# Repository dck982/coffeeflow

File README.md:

# coffeeflow

Modification d'une **Profitec Go** pour du *flow profiling* et du *brew by weight* : l'infusion se lance depuis un écran tactile, le débit et la pression se pilotent par la vitesse d'une **pompe à engrenage**, et l'infusion s'arrête toute seule au poids cible.

## Machine d'origine

- Vanne solénoïde trois voies + pompe vibratoire OLAB Silent Green 35 W (**remplacée** par une pompe à engrenage, voir plus bas) + boiler
- Petit boîtier PID : consigne / mesure de température du boiler, chrono
- Vanne OPV pour limiter la pression
- Plomberie en **1/8"**
- Connexions électriques internes : cosses à languette **FASTON 6,3 × 0,8 mm** (pas de piggyback : la dérivation se fait dans un boîtier imprimé)
- Deux compartiments : **technique** (hydraulique, boiler, groupe, électricité) et **réservoir d'eau**
- Bouton **brew** en façade (Ø 16 mm) : démarrait vanne + pompe. **Supprimé** — le trou sert de passe-câble vers l'écran
- LED de façade : ses cosses FASTON ont été réutilisées, la LED est réalimentée depuis le boîtier de l'alimentation

## Ce que la modification ajoute

La modification pilote la pompe, la vanne et la résistance de chaudière :

1. **Pompe** — la pompe vibratoire est remplacée par une **pompe à engrenage SOVOFLO MPB003** (moteur BLDC 24 V, 40 W, 0,1 ml par tour), installée le 12 novembre 2026. Volumétrique et sans pulsation, son débit suit la vitesse, commandée par une consigne 0–5 V et relue sur son tachymètre. Détail : [pompe-engrenage.md](docs/pompe-engrenage.md).
2. **Vanne solénoïde** — un triac sur la carte `combined` ouvre et ferme le circuit d'infusion.
3. **Chaudière** — le SSR Keysolu/Maxwell fourni avec la machine commande la résistance de chauffe ; `combined` lui envoie sa commande 5 V.

Plus de bouton brew, plus de relais NC de « mode manuel » : la commande passe par l'écran. Le système est alimenté dès que l'**interrupteur principal** de la machine est enfoncé.

Deux retours capteurs, sur la carte `combined` :

- **Pression** sur la plomberie, en amont de la vanne (XDB401 analogique, 0,4–2,4 V)
- **Débit** en amont de la pompe, côté basse pression (le capteur ne tient que 3 bar)

La pompe donne en plus sa **vitesse** par son tachymètre, donc le volume déplacé, au glissement près.

La **température de la chaudière** vient de la sonde NTC vissée en G1/8 dans la chaudière. Son câble rejoint le boîtier de l'écran, proche de la sonde, où un ADS1115 la mesure via un pont alimenté par le **3V3 et le GND du port Sensor AD du Waveshare**. Voir [la calibration NTC/ADS1115](docs/ntc_ads1115_calibration.md).

Le **poids** vient d'une balance **Acaia Lunar** en **BLE**, lue par l'écran. La pesée du drip tray par cellule de charge est **abandonnée pour l'instant** (peser quelques grammes sur un plateau d'un kilo) — notes dans `docs/driptray.md` ; les pièces imprimées ont été retirées (commit 1aa13ed). Une nouvelle balance intégrée au drip tray est en conception (cellule 1 kg, carte `pcb/scale`, pièces `print/parts/scale_*`) : [tray-with-scale.md](docs/tray-with-scale.md).

## Architecture électronique

**Une alimentation 24 V, une carte maison, deux nœuds ESP32-S3.** Le 230 V ne sort pas de la machine.

```
             interrupteur principal (230 V L/N)
                          │
                  [boitier_ps_24v]   intérieur, face ouest, le long du réservoir
               Wago L/N · alim 24 V 96 W
                  │            │    └── L/N → LED de façade
               L/N (J2)     24 V (J7) ──────────────→ pompe à engrenage MPB003
                  │            │                      (embouts doubles dans J7)
             [boitier_ac + boitier_dc]
              carte combined : XIAO ESP32-S3 · buck 24 → 5 V · CAN
                  │
                  ├── J3  triac ────────→ vanne solénoïde (230 V)
                  ├── J8  5 V ──────────→ SSR chaudière ─→ résistance
                  ├── J9  2 optocoupleurs ⇄ consigne et tachymètre de la pompe
                  ├── J10 ADS1115 ←──── capteur de pression XDB401 (0,4–2,4 V)
                  ├── J6  GPIO ←──────── débitmètre Digmesa
                  └── J1  5 V + CAN ───→ [screen_*] Waveshare 4,3" ESP32-S3
                                          UI · Wi-Fi · BLE
                                          └── I2C ← ADS1115 ← NTC chaudière
```

| Nœud | Alias | Où | Rôle |
| --- | --- | --- | --- |
| **Waveshare 4,3" LCD Touch** (ESP32-S3-WROOM) | *screen*, *écran*, *waveshare* | façade, dans `screen_base` + `screen_wedge` | Interface utilisateur, algorithme d'infusion, **Wi-Fi et BLE** (Acaia Lunar) ; raccordement de la NTC chaudière via ADS1115 |
| **Seeed XIAO ESP32-S3** sur la carte **`combined`** | *xiao*, *combined*, *module capteurs*, *contrôleur* | intérieur, `boitier_ac` + `boitier_dc`, zone froide entre le module PID et le cadran manomètre | Capteurs (XDB401, Digmesa, tachymètre) et actionneurs (consigne de la pompe, vanne, commande du SSR chaudière) |

Les deux nœuds parlent **CAN**. L'écran est le seul à utiliser la radio.

Maquette Three.js de la machine (ouvrir dans le navigateur) : `docs/profitec_go.html`.

### Pourquoi un XIAO à l'intérieur

L'Atom Echo S3R de l'ancienne architecture est spécifié à **40 °C**. Le XIAO ESP32-S3 tient **85 °C**. Le compartiment technique monte à 45–50 °C : la marge de l'Atom est nulle, celle du XIAO est utilisable. L'écran Waveshare reste en façade, hors de cette enceinte.

---

## Boîtiers

| Boîtier | Pièces `print/parts/` | Où | Contenu |
| --- | --- | --- | --- |
| **PS 24 V** | `boitier_ps_24v`, `couvercle_ps_24v` | intérieur, contre la face **gauche** vue de face, le long de la séparation avec le réservoir | Alimentation 24 V, deux Wago 221-415 (L, N) ; le câble de l'écran le traverse |
| **AC + DC** | `boitier_ac`, `boitier_dc`, `couvercle_acdc` | intérieur, **zone froide** entre le module PID et le cadran manomètre | Carte `combined` : bande secteur dans `boitier_ac`, basse tension et aile 24 V dans `boitier_dc` |
| **UI** | `screen_base`, `screen_wedge` | façade de la machine | Écran Waveshare 4,3", ADS1115 et raccordement NTC ; emplacement AMS1117 inutilisé |

Les boîtiers **AC et DC sont côte à côte et reliés par leur couvercle**, qui est commun aux deux (`couvercle_acdc`, assemblage `ensemble_boitiers`). `boitier_pid` ne loge plus rien : c'est un pont qui tient le `cache_pid` contre l'ouverture de la machine.

La pompe est fixée par son équerre d'origine dans deux des trous de 6 mm de la plaque du fond de la machine, à 40 mm d'entraxe.

---

## Composants

| Rôle | Matériel retenu | Fiche |
| --- | --- | --- |
| UI / algo / radio | **Waveshare ESP32-S3-Touch-LCD-4.3** — 800 × 480, TJA1051T/3 CAN intégré, alim USB-C 5 V | `docs/datasheets/waveshare-4-3-lcd-touch.md` |
| Carte interne | **`combined`** (maison, JLCPCB) : **Seeed Studio XIAO ESP32-S3** enfiché, buck 24 → 5 V, TJA1051T/3, triac de vanne, interface optocouplée de la pompe, ADS1115 de pression | `pcb/combined/combined_design.md`, `docs/datasheets/xiao.pdf` |
| Pompe | **SOVOFLO MPB003BAAA** — engrenage, BLDC 24 V 40 W, 0,1 ml/tour, 12 bar au plus, raccords G1/8 | [pompe-engrenage.md](docs/pompe-engrenage.md) |
| Alimentation | Module ouvert **24 V, 4 A** (Aideepen, 96 W), fusible T2A interne | [pompe-engrenage.md](docs/pompe-engrenage.md#alimentation), [boitier-ps-24v.md](docs/boitier-ps-24v.md) |
| SSR chaudière | **Keysolu/Maxwell KS53 D-24Z20N-LQ**, fourni avec la machine ; en série entre la phase de l'interrupteur principal et la résistance, suivie de la protection thermique puis du neutre ; commande DC +/− depuis `combined` J8, FASTON mâles 4,8 mm | [Câblage](docs/cablage.md#ssr-de-chaudière-fourni-avec-la-machine) |
| Température chaudière | Sonde **NTC G1/8**, pont sur le port Sensor AD et breakout **ADS1115 16 bits** sur l'I2C de l'écran | [Calibration NTC/ADS1115](docs/ntc_ads1115_calibration.md) |
| Pression | **XDB401** analogique, 3,3 V, sortie 0,4–2,4 V, 0–12 bar, filetage **G1/8** | `docs/xdb401_swap.md` |
| Débit | **Digmesa FHKSC 932-9525-B**, buse **1,00 mm** | `docs/datasheets/flowmeter-digmesa.pdf`, `docs/debitmetres.md` |
| Poids | **Acaia Lunar**, BLE, lue par l'écran | — |
| Câble | **Helutherm 145** — 0,75 mm² en 230 V et en 24 V, 0,5 mm² pour le Digmesa, 0,25 mm² pour le 5 V et le CAN de l'écran ; puissance chaudière en 1 mm² | `docs/datasheets/helutherm145.pdf` |

Actionneur d'origine piloté : vanne solénoïde **OLAB 08252L50-A14-1A-G** (bobine 08000BH-J5IV, 15 VA, 220/230 V 50/60 Hz, orifice Ø 1,4 mm, joint FKM, laiton CW510L, NSF).

---

## La carte `combined`

Une seule carte réunit la partie 230 V (vanne) et la basse tension (XIAO, CAN, capteurs, commande de la pompe et du SSR chaudière). Elle reçoit le 24 V de l'alimentation et fait son propre 5 V, qu'elle renvoie à l'écran avec le CAN.

| Connecteur | Type | Vers |
| --- | --- | --- |
| **J1** | XH 4 | écran : GND, +5V, CAN_L, CAN_H |
| **J2** | HT3.96 2 | entrée 230 V, L et N |
| **J3** | HT3.96 2 | vanne solénoïde |
| **J6** | HT3.96 3 | Digmesa |
| **J7** | HT3.96 2 | entrée 24 V ; la pompe y est alimentée par des embouts doubles |
| **J8** | HT3.96 2 | commande du SSR chaudière |
| **J9** | XH 4 | signaux de la pompe : référence, consigne, tachymètre, 5 V de la pompe |
| **J10** | XH 3 | XDB401 |

J4 et J5, les prises I2C Grove de la carte `sensors`, n'existent plus. Brochage, schéma et choix des composants : `pcb/combined/combined_design.md`. Détail fil par fil : [cablage.md](docs/cablage.md).

**Pompe.** La consigne passe par un optocoupleur et un filtre RC (PWM à 1 kHz), le tachymètre revient par un second optocoupleur : les fils de signal de la pompe ne touchent jamais une masse ni une alimentation de la carte. Sans commande (démarrage, reset, XIAO absent), la consigne retombe à 0 et la pompe reste à l'arrêt.

**Bus CAN.** Paire torsadée de J1 jusqu'à l'écran, par le trou de l'ancien bouton brew. **Terminaisons 120 Ω aux deux bouts** : soudée sur `combined`, par jumper sur le Waveshare.

---

## Alimentation

L'**alimentation 24 V, 96 W** vit dans `boitier_ps_24v` et alimente **tout** : la pompe directement, et toute la basse tension par le buck de `combined`.

### 230 V

- **Phase et neutre** viennent de deux **cosses FASTON isolées** prises sur l'**interrupteur principal** de la machine : tant qu'il n'est pas enfoncé (clic mécanique), rien n'est sous tension.
- Les deux fils (**Helutherm 145 0,75 mm²**) vont dans les deux **Wago 221-415** de `boitier_ps_24v`, une pour L, une pour N.
- De ces Wago repartent trois paires 0,75 mm² : la **LED de façade**, l'**alimentation 24 V** (JST VH, position centrale vide) et **`combined` J2** (HT3.96).
- De **J3** repartent phase commutée et neutre vers la **vanne solénoïde** — **bleu / jaune**, FASTON 6,3 mm côté vanne.

### 24 V

- Deux fils **0,75 mm² rouge / noir** vont du bornier de l'alimentation à **`combined` J7**.
- Dans le boîtier HT3.96 de J7, chaque fil est serti avec le fil de même polarité de la pompe dans un **embout double 2 × 0,75 mm²** : la pompe est alimentée par J7, sans que son courant traverse les pistes de la carte.
- Le buck de `combined` fait le **5 V** du XIAO, du CAN, du Digmesa, de la commande du SSR chaudière et de l'**écran**, par J1 : paire 5 V / GND le long de la paire CAN, puis deux Wago 221-412 et un câble USB-C côté écran.
- Le pont NTC du boîtier de l'écran utilise le **3V3 / GND du port Sensor AD du Waveshare**.

---

## Capteurs

### Température chaudière — NTC G1/8

La sonde rejoint directement le boîtier de l'écran, voisin de la chaudière. Le **3V3 du port Sensor AD du Waveshare** rejoint la Wago NTC2, la NTC et l'entrée **A0** de l'ADS1115 ; le retour NTC rejoint la Wago NTC1, **A1** et une résistance de **4,7 kΩ** (4676 Ω étalonnés) vers le **GND du même port Sensor AD**. L'ADS1115 16 bits est sur le port I2C du Waveshare. A0 permet de mesurer la tension réelle d'alimentation du pont. Schéma et paramètres de conversion : [calibration NTC/ADS1115](docs/ntc_ads1115_calibration.md).

### Pression — XDB401 analogique

Trois fils : **rouge 3,3 V**, **noir GND**, **jaune sortie 0,4–2,4 V**, sertis en JST XH sur **J10** de `combined`. Sortie non ratiométrique, 6 bar/V, lue par l'ADS1115 de la carte ; l'écran reçoit la pression par le CAN. Filetage **G1/8**, d'où le choix (plomberie machine en 1/8"). Gaine silicone avec une fine feuille de blindage, sans continuité avec le GND : elle reste flottante. Passage de la sonde I2C à la sonde analogique : `docs/xdb401_swap.md`.

### Débit — Digmesa FHKSC 932-9525-B (buse 1,00 mm)

| | 932-9525-B (retenu) | 932-9521-A (ancien) |
| --- | --- | --- |
| Buse | **1,00 mm** | 1,20 mm |
| Sens de montage | 0° | 0° |
| Impulsions | **2382 imp/L (0,42 g)** | 1925 imp/L (0,519 g) |
| Plage linéaire | **0,033 – 0,40 L/min** | 0,075 – 0,569 L/min |
| Pré-infusion 0,5 g/s | bas de plage | sous le linéaire |
| Perte de charge | ~0,48 bar vers 0,40 L/min | ~0,42 bar à 0,6 L/min |
| **Pression max** | **3 bar à 20 °C** | 3 bar à 20 °C |

Deux conséquences qui ne relèvent pas du câblage :

- **Le capteur va en amont de la pompe**, entre le réservoir et son entrée. La machine infuse à 9 bar et la pompe monte plus haut avant l'OPV : 3 bar de tenue interdisent le circuit haute pression.
- Le **1,00 mm** met une extraction de 36 g / 28 s (0,077 L/min) à 2,3 × son minimum, et 0,5 g/s au début du linéaire. Plafond 0,40 L/min : la pompe le dépasse à basse pression au-delà de 4 000 tr/min. Le débit se lit alors sur le tachymètre ; le Digmesa sert surtout à mesurer le glissement de la pompe. Comparatif complet : `docs/debitmetres.md`.

---

## Câblage

| Domaine | Fil | Connectique |
| --- | --- | --- |
| 230 V — arrivée, LED, alimentation, `combined`, vanne | **Helutherm 145 0,75 mm²**, paires L/N sous gaine thermo | Wago 221-415 ; FASTON 6,3 × 0,8 mm côté machine ; HT3.96 côté `combined` |
| 230 V — puissance chaudière | **1 mm²** | SSR chaudière fourni avec la machine, FASTON mâles 4,8 mm |
| 24 V et commande du SSR chaudière | **Helutherm 145 0,75 mm²** | HT3.96 à embouts ; bornier de l'alimentation ; cosses 4,8 mm côté SSR |
| Digmesa | **Helutherm 145 0,5 mm²** | HT3.96 côté `combined`, VH3.96 côté capteur |
| 5 V / CAN de l'écran | **Helutherm 145 0,25 mm²** | JST XH, JST SM, JST PH 2.0, Wago 221-412, USB-C |
| Pompe (signaux), XDB401 | câbles intégrés | JST XH serti sur les fils d'origine |

Détail fil par fil, couleurs et cheminement : `docs/cablage.md`. Passage intérieur → façade : le trou **Ø 16 mm** de l'ancien bouton brew, avec le passe-câble imprimé.

## Firmware

- **`combined` (XIAO ESP32-S3)** — consigne PWM et tachymètre de la pompe, commande de la vanne et du SSR chaudière, ADS1115 de pression, comptage d'impulsions du débitmètre, TWAI/CAN. Le crate garde le nom `sensors`, la carte qu'il pilotait avant `combined`.
- **UI (Waveshare ESP32-S3)** — affichage et commandes, **algorithme d'infusion** (flow control, stop on weight), Wi-Fi, BLE vers l'Acaia Lunar. L'ADS1115 sur son I2C mesure la température chaudière par une NTC.

**Langage : Rust** (`no_std`, esp-hal, embassy) sur les deux cartes, sous `firmware/rust/` ; l'interface de l'écran est en **Slint**. Le firmware C++/ESP-IDF d'origine est archivé dans `archive/firmware/`, toujours compilable : il reste la référence de comportement sur le bus CAN et en HTTP. L'outil Mac `coffeetool` (Rust) remplace les scripts Python, archivés eux aussi.

**État du firmware (2026-11-12) :** écran et `combined` en **0.5.0**, installés sur la machine avec la pompe à engrenage. Démarrage, CAN et montée en température vérifiés ; la première purge attend le séchage du Loxeal des raccords de la pompe. Voir [le contrat firmware](docs/firmware.md) et [la calibration NTC](docs/ntc_ads1115_calibration.md).

Conception, protocole CAN et sécurité : `docs/firmware.md`. Build, flash et banc : `docs/firmware-build.md`. Style et structure de l'interface tactile : `docs/ui.md`, maquette à l'échelle `docs/ui-mockup.html`.

## Disposition mécanique

- **`boitier_ps_24v`** — intérieur, contre la face gauche vue de face, le long de la séparation avec le réservoir.
- **`boitier_dc` + `boitier_ac`** — intérieur, zone froide entre le module PID et le cadran manomètre ; côte à côte, couvercle commun ; ils logent la carte `combined`.
- **Pompe** — équerre d'origine vissée dans deux trous de 6 mm de la plaque du fond, à 40 mm d'entraxe.
- **UI** — façade, à l'emplacement des boutons. Le wedge cadre l'écran (vissé par l'arrière), la base accueille le wedge (`screen_assembly`).

Pas de perçage du châssis : aimants Ø8 × 3 mm à l'intérieur, trou brew existant vers l'extérieur, trous existants de la plaque du fond pour la pompe.

### Pièces imprimées (`print/`)

Projet [nurb](https://pypi.org/project/nurb/) : lancer `nurb` depuis `print/`. Export préféré : **3MF** dans `print/build/`. Sur cette machine, pour tout script Python (y compris hors `print/`) : **`uv run`**, pas le `python` système — détail dans `print/README.md`.

| Pièce | Où | Rôle |
| --- | --- | --- |
| `boitier_ps_24v` / `couvercle_ps_24v` | intérieur, face ouest | Alimentation 24 V, Wago 230 V |
| `boitier_dc` | intérieur, zone froide | Partie basse tension et aile 24 V de `combined` |
| `boitier_ac` | accolé au DC | Bande secteur de `combined` (J2, J3) |
| `couvercle_acdc` | — | Couvercle unique des deux boîtiers |
| `ensemble_boitiers` | — | Assemblage DC + AC |
| `boitier_pid` / `cache_pid` | compartiment technique | Pont qui tient le cache contre l'ouverture du module PID |
| `screen_wedge` / `screen_base` | façade | Cadre de l'écran Waveshare (vis M2.5 à l'arrière) et son berceau |
| `passe_cable` / `ecrou_passe_cable` | façade | Traversée du trou Ø 16 mm ex-bouton brew |
| `canal` | intérieur | Guidage des fils |

### Wago

Côté machine : FASTON 6,3 × 0,8 mm isolées nylon. Côté mod : Wago 221 (412, 415 selon l'emplacement) et connecteurs HT3.96 sur `combined`. Pas de piggyback. Vis M3, inserts laiton M2 et M2.5 pour les cartes. Aimants 8 × 3 mm. Wago sans contact avec le fond ni les parois.

## Matière d'impression

**Les boîtiers sont imprimés en PLA HT recuit** — après recuit, la tenue en température monte à **140 °C**, très au-dessus des 40–50 °C du compartiment technique et sans le fluage du PLA standard à partir de ~45 °C. La machine tourne 10–15 min, deux fois par jour ; le reste du temps tout est à température ambiante et hors tension.

Le recuit fait retirer les pièces : les cotes fit-critiques (puits d'aimant, logements Wago, inserts) se vérifient **après** recuit, pas sur la pièce sortie du plateau.

*Atelier : Bambu Lab A1 Mini.*

## Dépôt

```
coffeeflow/
  README.md          ← cette vue d'ensemble
  docs/              ← câblage, débitmètres, drip tray et sa balance, maquettes Three.js ; datasheets/
  firmware/rust/     ← firmwares écran et capteurs, protocole CAN, coffeetool (Rust)
  archive/firmware/  ← firmware C++/ESP-IDF d'origine et outils Python (référence)
  print/             ← impressions 3D (nurb)
  tests/             ← scripts MicroPython de banc
  sound_test/        ← sketch Arduino de test Atom S3 (reliquat)
  tts/               ← génération WAV (Gemini TTS) pour le sketch
```

Contraintes et cotes d'une pièce : `print/parts/<nom>.md` + `print/measurements.toml`.

## Banc

Multimètre : **M5Stack Atom Echo S3R** + **Unit VMeter** (Grove PORT.A, ±36 V DC, bornes vis). Script `tests/test_vmeter.py`. Ne pas mesurer au GPIO de l'ESP32 (3,3 V max, pas 5 V).

## Sketch de test (`sound_test/`)

Reliquat Atom S3 Voice (Echo), ESP32-S3, USB-CDC natif, `M5.Speaker`, bouton `M5.BtnA`. FQBN : `m5stack:esp32:m5stack_atoms3`.

```
ls /dev/cu.usbmodem*
arduino-cli compile --fqbn m5stack:esp32:m5stack_atoms3 sound_test
arduino-cli upload -p /dev/cu.usbmodem2201 --fqbn m5stack:esp32:m5stack_atoms3 sound_test
```

Câble USB-C **data**. Si le port n'apparaît pas : autre câble, pas de hub, reset latéral. Le suffixe `usbmodem*` change à chaque reconnexion.

## TTS (`tts/`)

```
cd tts
uv run generate_tts.py "Espresso ready" -o startup.wav
```

Clé `GOOGLE_API_KEY` dans `tts/.env` (non commité). Pour embarquer le WAV :

```
xxd -i tts/startup.wav | sed 's/tts_startup_wav/startup_wav/; s/unsigned char/const uint8_t/; s/unsigned int/const unsigned int/' > sound_test/startup_wav.h
```

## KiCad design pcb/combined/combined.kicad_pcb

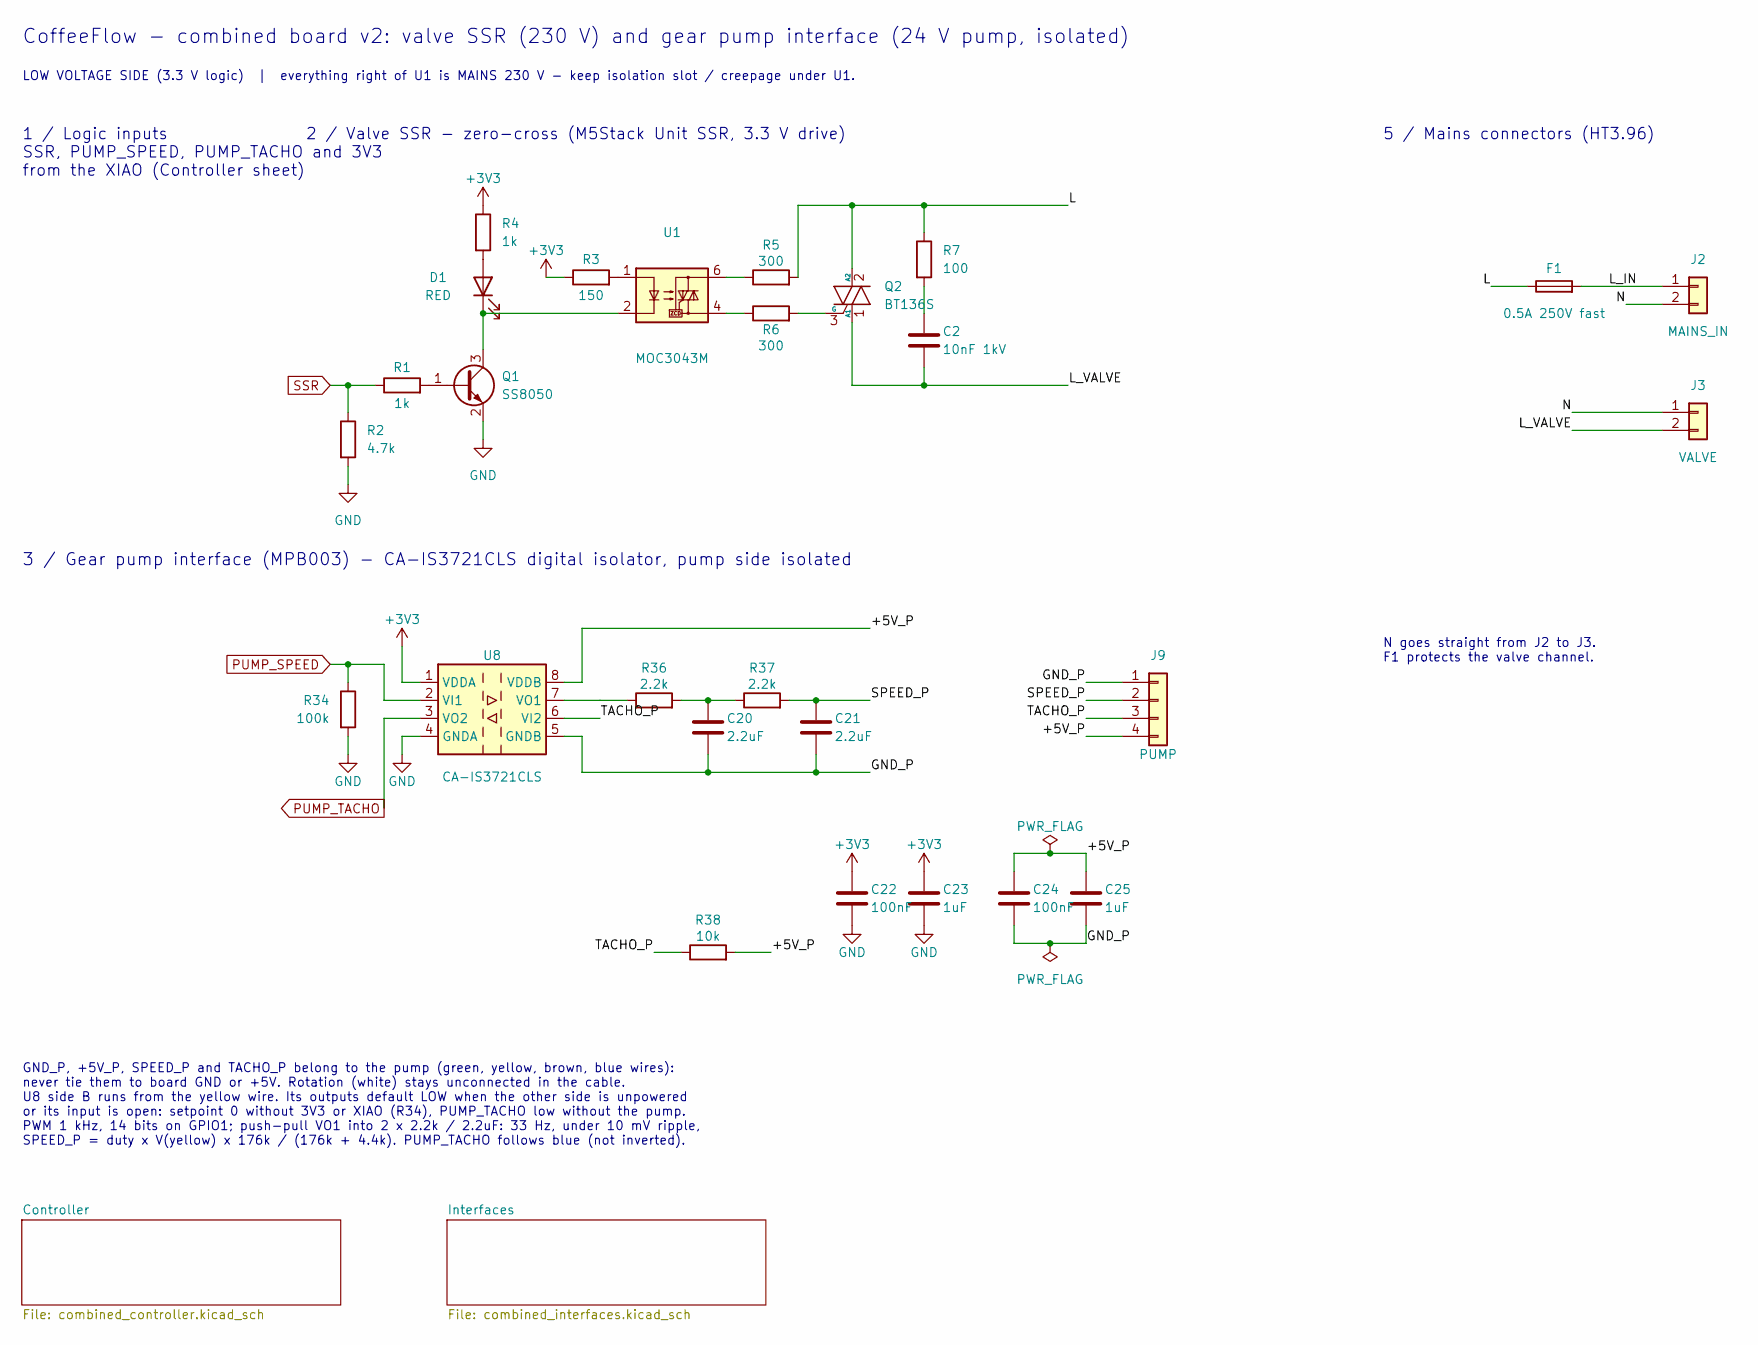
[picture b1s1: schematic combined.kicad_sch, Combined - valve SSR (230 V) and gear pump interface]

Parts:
C2: 10nF 1kV; C_1812_4532Metric; MPN FV43X103K102EFG; LCSC C394164
C20, C21: 2.2uF; C_0805_2012Metric; MPN CL21A225KBQNNNE; LCSC C377773
C22, C24: 100nF; C_0603_1608Metric; MPN CC0603KRX7R9BB104; LCSC C14663
C23, C25: 1uF; C_0805_2012Metric; MPN CL21B105KBFNNNE; LCSC C28323
D1: RED; LED_0603_1608Metric; MPN KT-0603R; LCSC C2286
F1: 0.5A 250V fast; F2410; MPN MF2410F0.500TM; LCSC C91409
J2: MAINS_IN; CONN-TH_P3.96_HT396R-3.96-2P; MPN MXHT396R-3.96-02P-OE01-Cu-A; LCSC C48688287
J3: VALVE; CONN-TH_P3.96_HT396R-3.96-2P; MPN MXHT396R-3.96-02P-OE01-Cu-A; LCSC C48688287
J9: PUMP; JST_XH_B4B-XH-A_1x04_P2.50mm_Vertical; MPN B4B-XH-A(LF)(SN); LCSC C144395
Q1: SS8050; SOT-23; MPN SS8050 (Y1); LCSC C2150
Q2: BT136S; TO-252-2; MPN BT136S; LCSC C23427
R1, R4: 1k; R_0603_1608Metric; MPN 0603WAF1001T5E; LCSC C21190
R2: 4.7k; R_0603_1608Metric; MPN 0603WAF4701T5E; LCSC C23162
R3: 150; R_0603_1608Metric; MPN 0603WAF1500T5E; LCSC C22808
R5, R6: 300; R_1206_3216Metric; MPN 1206W4F3000T5E; LCSC C17887
R7: 100; R_1206_3216Metric; MPN 1206W4F1000T5E; LCSC C17901
R34: 100k; R_0603_1608Metric; MPN 0603WAF1003T5E; LCSC C25803
R36, R37: 2.2k; R_0603_1608Metric; MPN 0603WAF2201T5E; LCSC C4190
R38: 10k; R_0603_1608Metric; MPN 0603WAF1002T5E; LCSC C25804
U1: MOC3043M; SMDIP-6_W9.53mm_Slot; MPN MOC3043SR2M; LCSC C41809
U8: CA-IS3721CLS; SOIC-8_3.9x4.9mm_P1.27mm; MPN CA-IS3721CLS; LCSC C41784135

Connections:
+3V3: C22.1, C23.1, R3.1, R4.1, U8.1 (VDDA); also elsewhere on the board
/+5V_P: C24.1, C25.1, J9.4, R38.2, U8.8 (VDDB)
/GND_P: C20.2, C21.2, C24.2, C25.2, J9.1, U8.5 (GNDB)
/L: F1.1, Q2.2 (A2), R5.2, R7.1
/L_IN: F1.2, J2.1
/L_VALVE: C2.2, J3.2, Q2.1 (A1)
/N: J2.2, J3.1
/SPEED_P: C21.1, J9.2, R37.2
/TACHO_P: J9.3, R38.1, U8.6 (VI2)
GND: C22.2, C23.2, Q1.2 (E), R2.2, R34.2, U8.4 (GNDA); also elsewhere on the board
unnamed: C2.1, R7.2
unnamed: C20.1, R36.2, R37.1
unnamed: D1.2 (A), R4.2
unnamed: D1.1 (K), Q1.3 (C), U1.2
unnamed: Q1.1 (B), R1.2
unnamed: Q2.3 (G), R6.2
unnamed: R3.2, U1.1
unnamed: R5.1, U1.6
unnamed: R6.1, U1.4
unnamed: R36.1, U8.7 (VO1)
PUMP_SPEED: R34.1, U8.2 (VI1); also elsewhere on the board
PUMP_TACHO: U8.3 (VO2); also elsewhere on the board
SSR: R1.1, R2.1; also elsewhere on the board

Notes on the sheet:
2 / Valve SSR - zero-cross (M5Stack Unit SSR, 3.3 V drive)
5 / Mains connectors (HT3.96)
1 / Logic inputs SSR, PUMP_SPEED, PUMP_TACHO and 3V3 from the XIAO (Controller sheet)
N goes straight from J2 to J3. F1 protects the valve channel.
CoffeeFlow - combined board v2: valve SSR (230 V) and gear pump interface (24 V pump, isolated)
LOW VOLTAGE SIDE (3.3 V logic) | everything right of U1 is MAINS 230 V - keep isolation slot / creepage under U1.
3 / Gear pump interface (MPB003) - CA-IS3721CLS digital isolator, pump side isolated
GND_P, +5V_P, SPEED_P and TACHO_P belong to the pump (green, yellow, brown, blue wires): never tie them to board GND or +5V. Rotation (white) stays unconnected in the cable. U8 side B runs from the yellow wire. Its outputs default LOW when the other side is unpowered or its input is open: setpoint 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

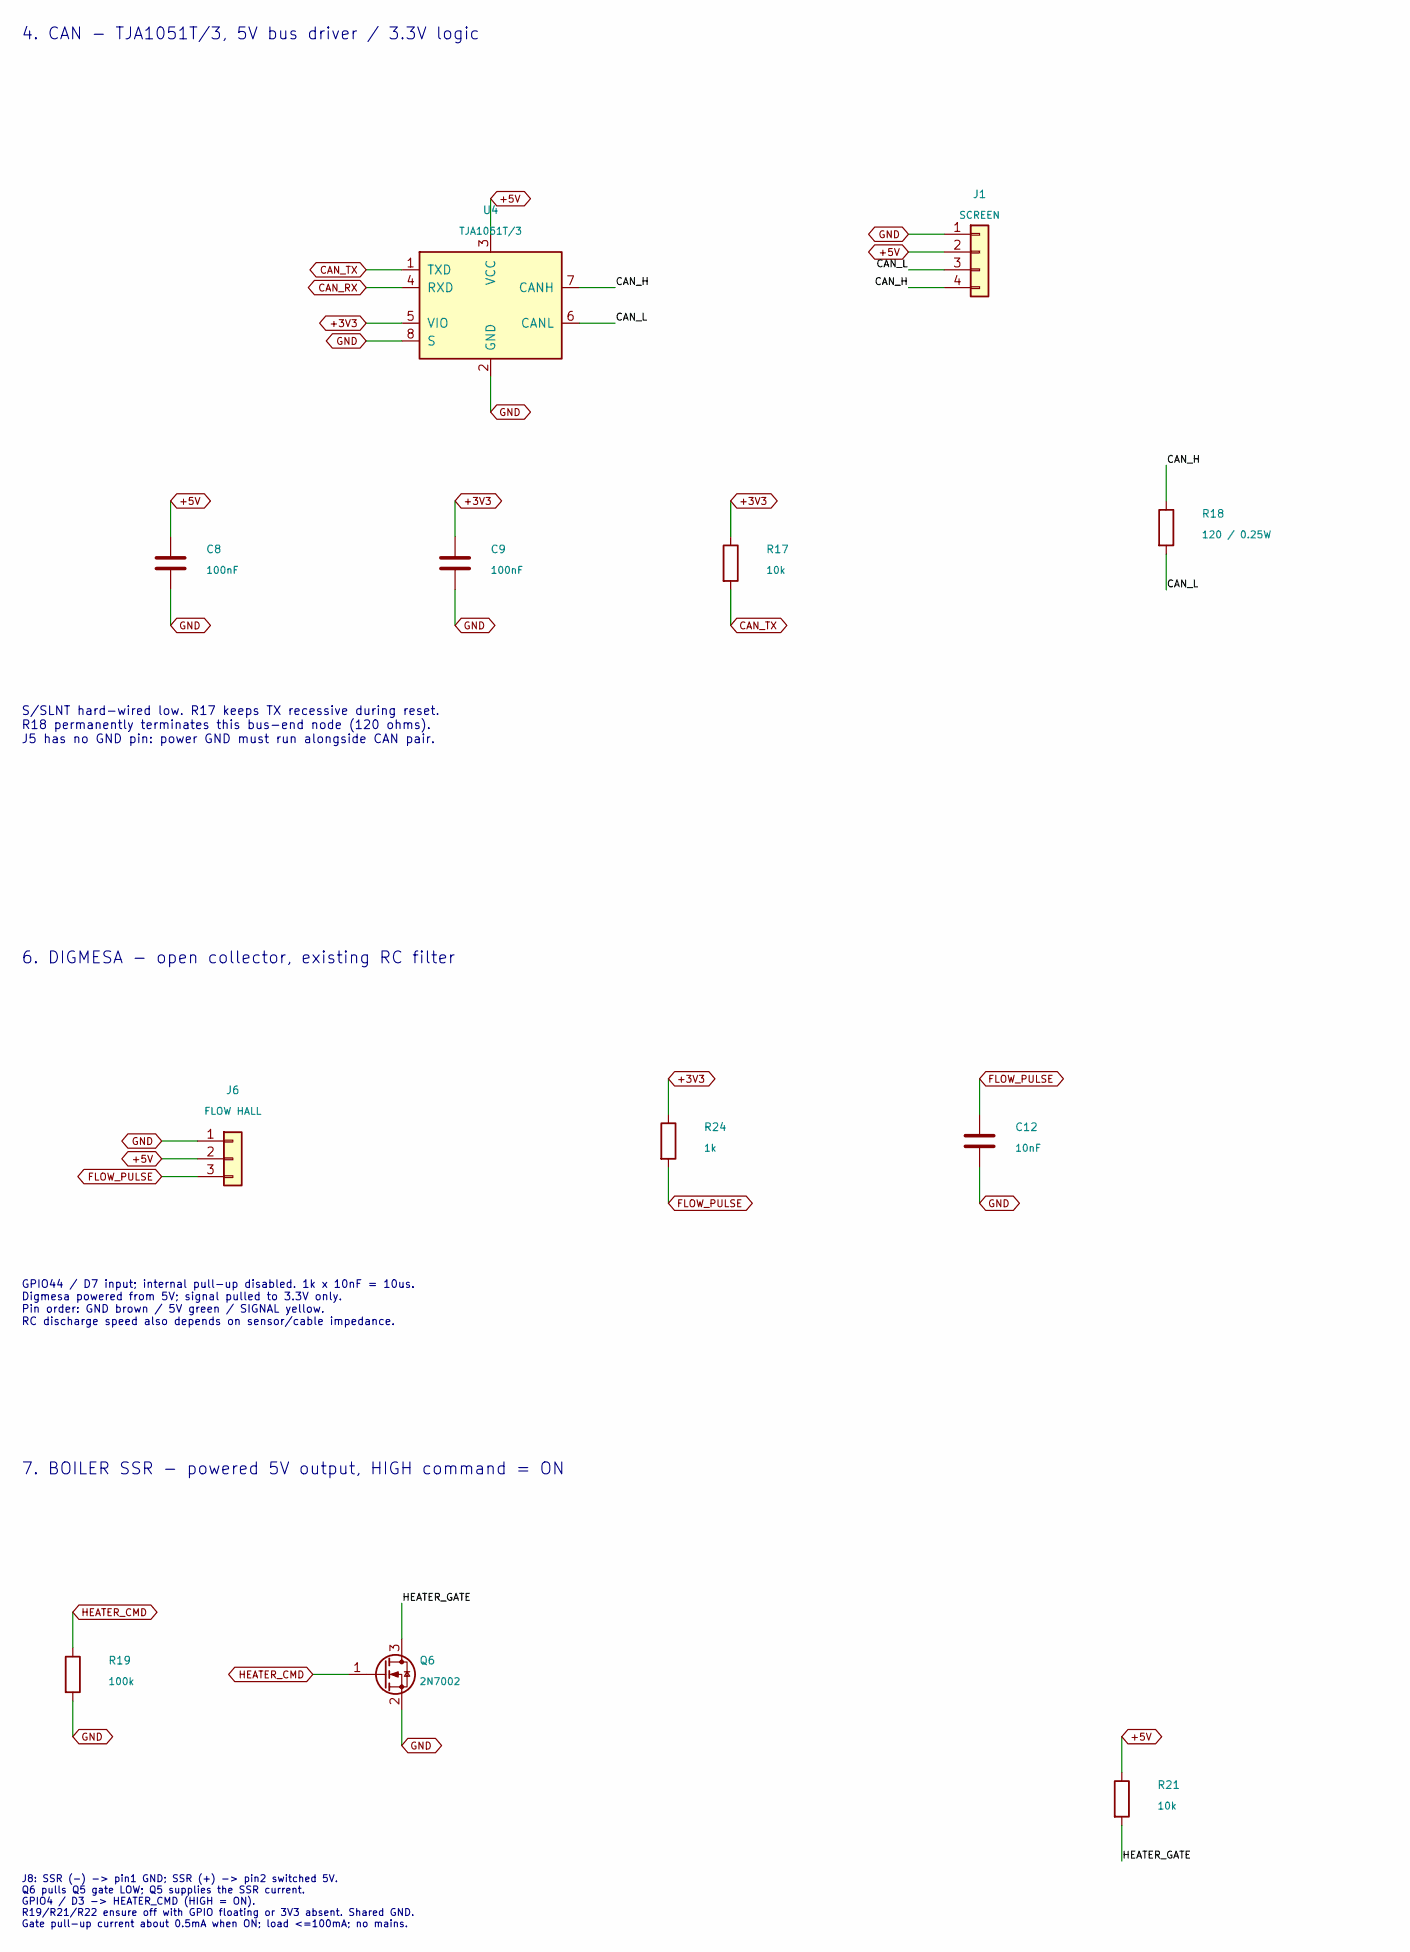
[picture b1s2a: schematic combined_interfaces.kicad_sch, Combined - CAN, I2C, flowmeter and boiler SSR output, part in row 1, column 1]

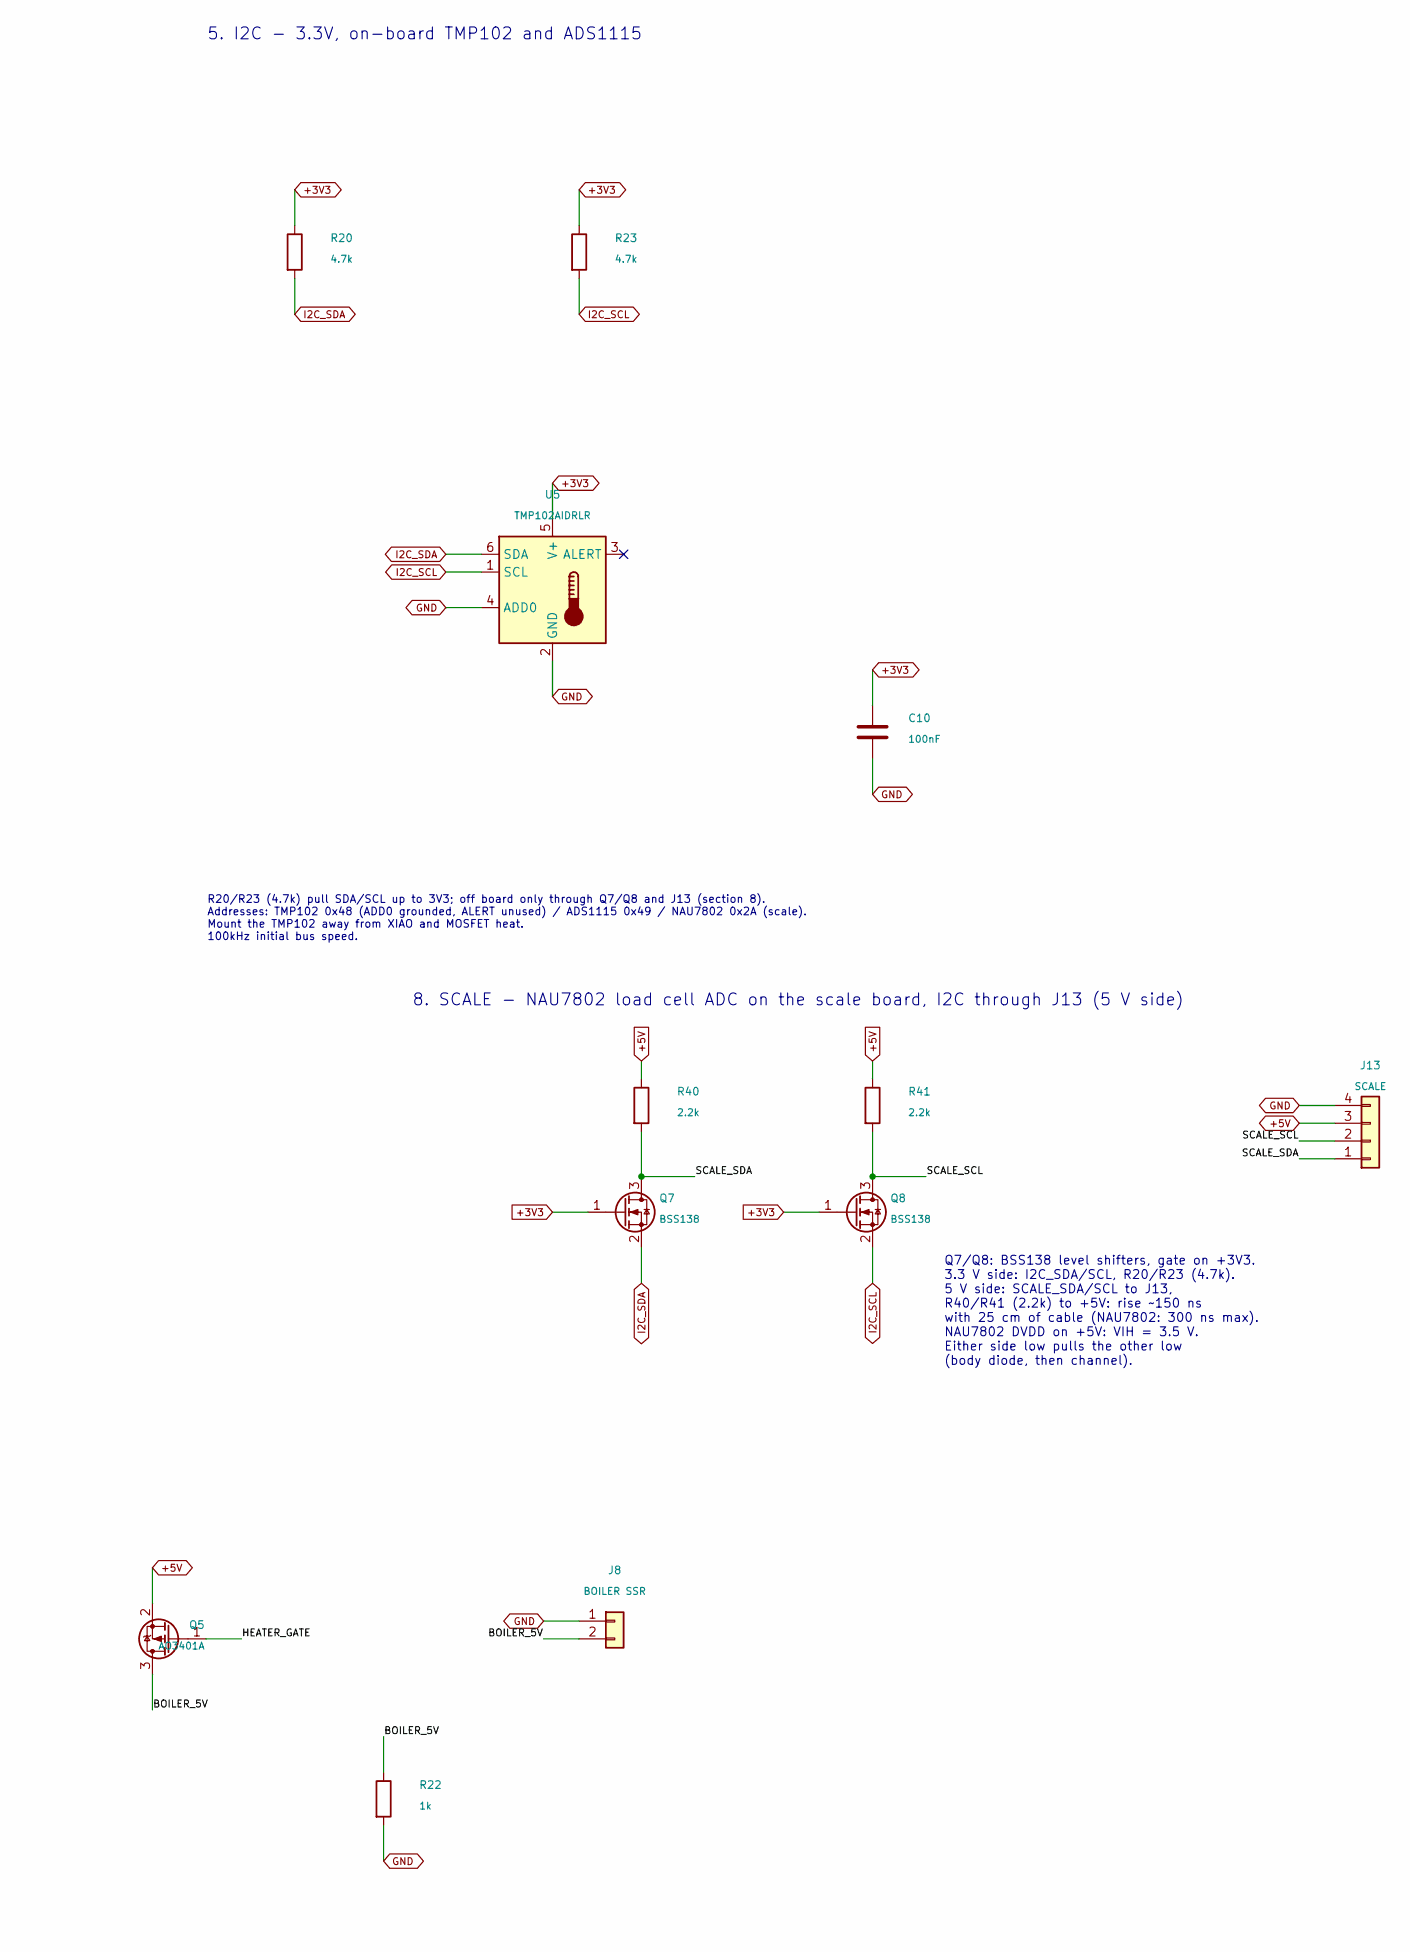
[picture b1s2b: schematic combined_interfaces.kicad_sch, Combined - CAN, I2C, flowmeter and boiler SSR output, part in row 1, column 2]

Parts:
C8, C9, C10: 100nF; C_0603_1608Metric; MPN CC0603KRX7R9BB104; LCSC C14663
C12: 10nF; C_0603_1608Metric; MPN 0603B103K500NT; LCSC C57112
J1: SCREEN; JST_XH_B4B-XH-A_1x04_P2.50mm_Vertical; MPN B4B-XH-A(LF)(SN); LCSC C144395
J6: FLOW HALL; CONN-TH_P3.96_HT396V-3.96-3P; MPN HT396V-3.96-3P; LCSC C577789
J8: BOILER SSR; CONN-TH_P3.96_HT396V-3.96-2P; MPN HT396V-3.96-2P; LCSC C577788
J13: SCALE; JST_XH_B4B-XH-A_1x04_P2.50mm_Vertical; MPN B4B-XH-A(LF)(SN); LCSC C144395
Q5: AO3401A; SOT-23; MPN AO3401A; LCSC C15127
Q6: 2N7002; SOT-23; MPN 2N7002; LCSC C8545
Q7, Q8: BSS138; SOT-23; MPN BSS138-7-F; LCSC C40912
R17, R21: 10k; R_0603_1608Metric; MPN 0603WAF1002T5E; LCSC C25804
R18: 120 / 0.25W; R_1206_3216Metric; MPN 1206W4F1200T5E; LCSC C17909
R19: 100k; R_0603_1608Metric; MPN 0603WAF1003T5E; LCSC C25803
R20, R23: 4.7k; R_0603_1608Metric; MPN 0603WAF4701T5E; LCSC C23162
R22, R24: 1k; R_0603_1608Metric; MPN 0603WAF1001T5E; LCSC C21190
R40, R41: 2.2k; R_0603_1608Metric; MPN 0603WAF2201T5E; LCSC C4190
U4: TJA1051T/3; SOIC-8_3.9x4.9mm_P1.27mm; MPN TJA1051T/3/1J; LCSC C38695
U5: TMP102AIDRLR; SOT-563; MPN TMP102AIDRLR; LCSC C99269

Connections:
+3V3: C9.1, C10.1, Q7.1 (G), Q8.1 (G), R17.1, R20.1, R23.1, R24.1, U4.5 (VIO), U5.5 (V+); also elsewhere on the board
+5V: C8.1, J1.2, J6.2, J13.3, Q5.2 (S), R21.1, R40.1, R41.1, U4.3 (VCC); also elsewhere on the board
/Interfaces/BOILER_5V: J8.2, Q5.3 (D), R22.1
/Interfaces/CAN_H: J1.4, R18.1, U4.7 (CANH)
/Interfaces/CAN_L: J1.3, R18.2, U4.6 (CANL)
/Interfaces/HEATER_GATE: Q5.1 (G), Q6.3 (D), R21.2
/Interfaces/SCALE_SCL: J13.2, Q8.3 (D), R41.2
/Interfaces/SCALE_SDA: J13.1, Q7.3 (D), R40.2
CAN_RX: U4.4 (RXD); also elsewhere on the board
CAN_TX: R17.2, U4.1 (TXD); also elsewhere on the board
FLOW_PULSE: C12.1, J6.3, R24.2; also elsewhere on the board
GND: C8.2, C9.2, C10.2, C12.2, J1.1, J6.1, J8.1, J13.4, Q6.2 (S), R19.2, R22.2, U4.2 (GND), U4.8 (S), U5.2 (GND), U5.4 (ADD0); also elsewhere on the board
HEATER_CMD: Q6.1 (G), R19.1; also elsewhere on the board
I2C_SCL: Q8.2 (S), R23.2, U5.1 (SCL); also elsewhere on the board
I2C_SDA: Q7.2 (S), R20.2, U5.6 (SDA); also elsewhere on the board

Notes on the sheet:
7. BOILER SSR - powered 5V output, HIGH command = ON
5. I2C - 3.3V, on-board TMP102 and ADS1115
4. CAN - TJA1051T/3, 5V bus driver / 3.3V logic
6. DIGMESA - open collector, existing RC filter
R20/R23 (4.7k) pull SDA/SCL up to 3V3; off board only through Q7/Q8 and J13 (section 8). Addresses: TMP102 0x48 (ADD0 grounded, ALERT unused) / ADS1115 0x49 / NAU7802 0x2A (scale). Mount the TMP102 away from XIAO and MOSFET heat. 100kHz initial bus speed.
S/SLNT hard-wired low. R17 keeps TX recessive during reset. R18 permanently terminates this bus-end node (120 ohms). J5 has no GND pin: power GND must run alongside CAN pair.
J8: SSR (-) -> pin1 GND; SSR (+) -> pin2 switched 5V. Q6 pulls Q5 gate LOW; Q5 supplies the SSR current. GPIO4 / D3 -> HEATER_CMD (HIGH = ON). R19/R21/R22 ensure off with GPIO floating or 3V3 absent. Shared GND. Gate pull-up current about 0.5mA when ON; load <=100mA; no mains.
GPIO44 / D7 input; internal pull-up disabled. 1k x 10nF = 10us. Digmesa powered from 5V; signal pulled to 3.3V only. Pin order: GND brown / 5V green / SIGNAL yellow. RC discharge speed also depends on sensor/cable impedance.
8. SCALE - NAU7802 load cell ADC on the scale board, I2C through J13 (5 V side)
Q7/Q8: BSS138 level shifters, gate on +3V3. 3.3 V side: I2C_SDA/SCL, R20/R23 (4.7k). 5 V side: SCALE_SDA/SCL to J13, R40/R41 (2.2k) to +5V: rise ~150 ns with 25 cm of cable (NAU7802: 300 ns max). NAU7802 DVDD on +5V: VIH = 3.5 V. Either side low pulls the other low (body diode, then channel).
